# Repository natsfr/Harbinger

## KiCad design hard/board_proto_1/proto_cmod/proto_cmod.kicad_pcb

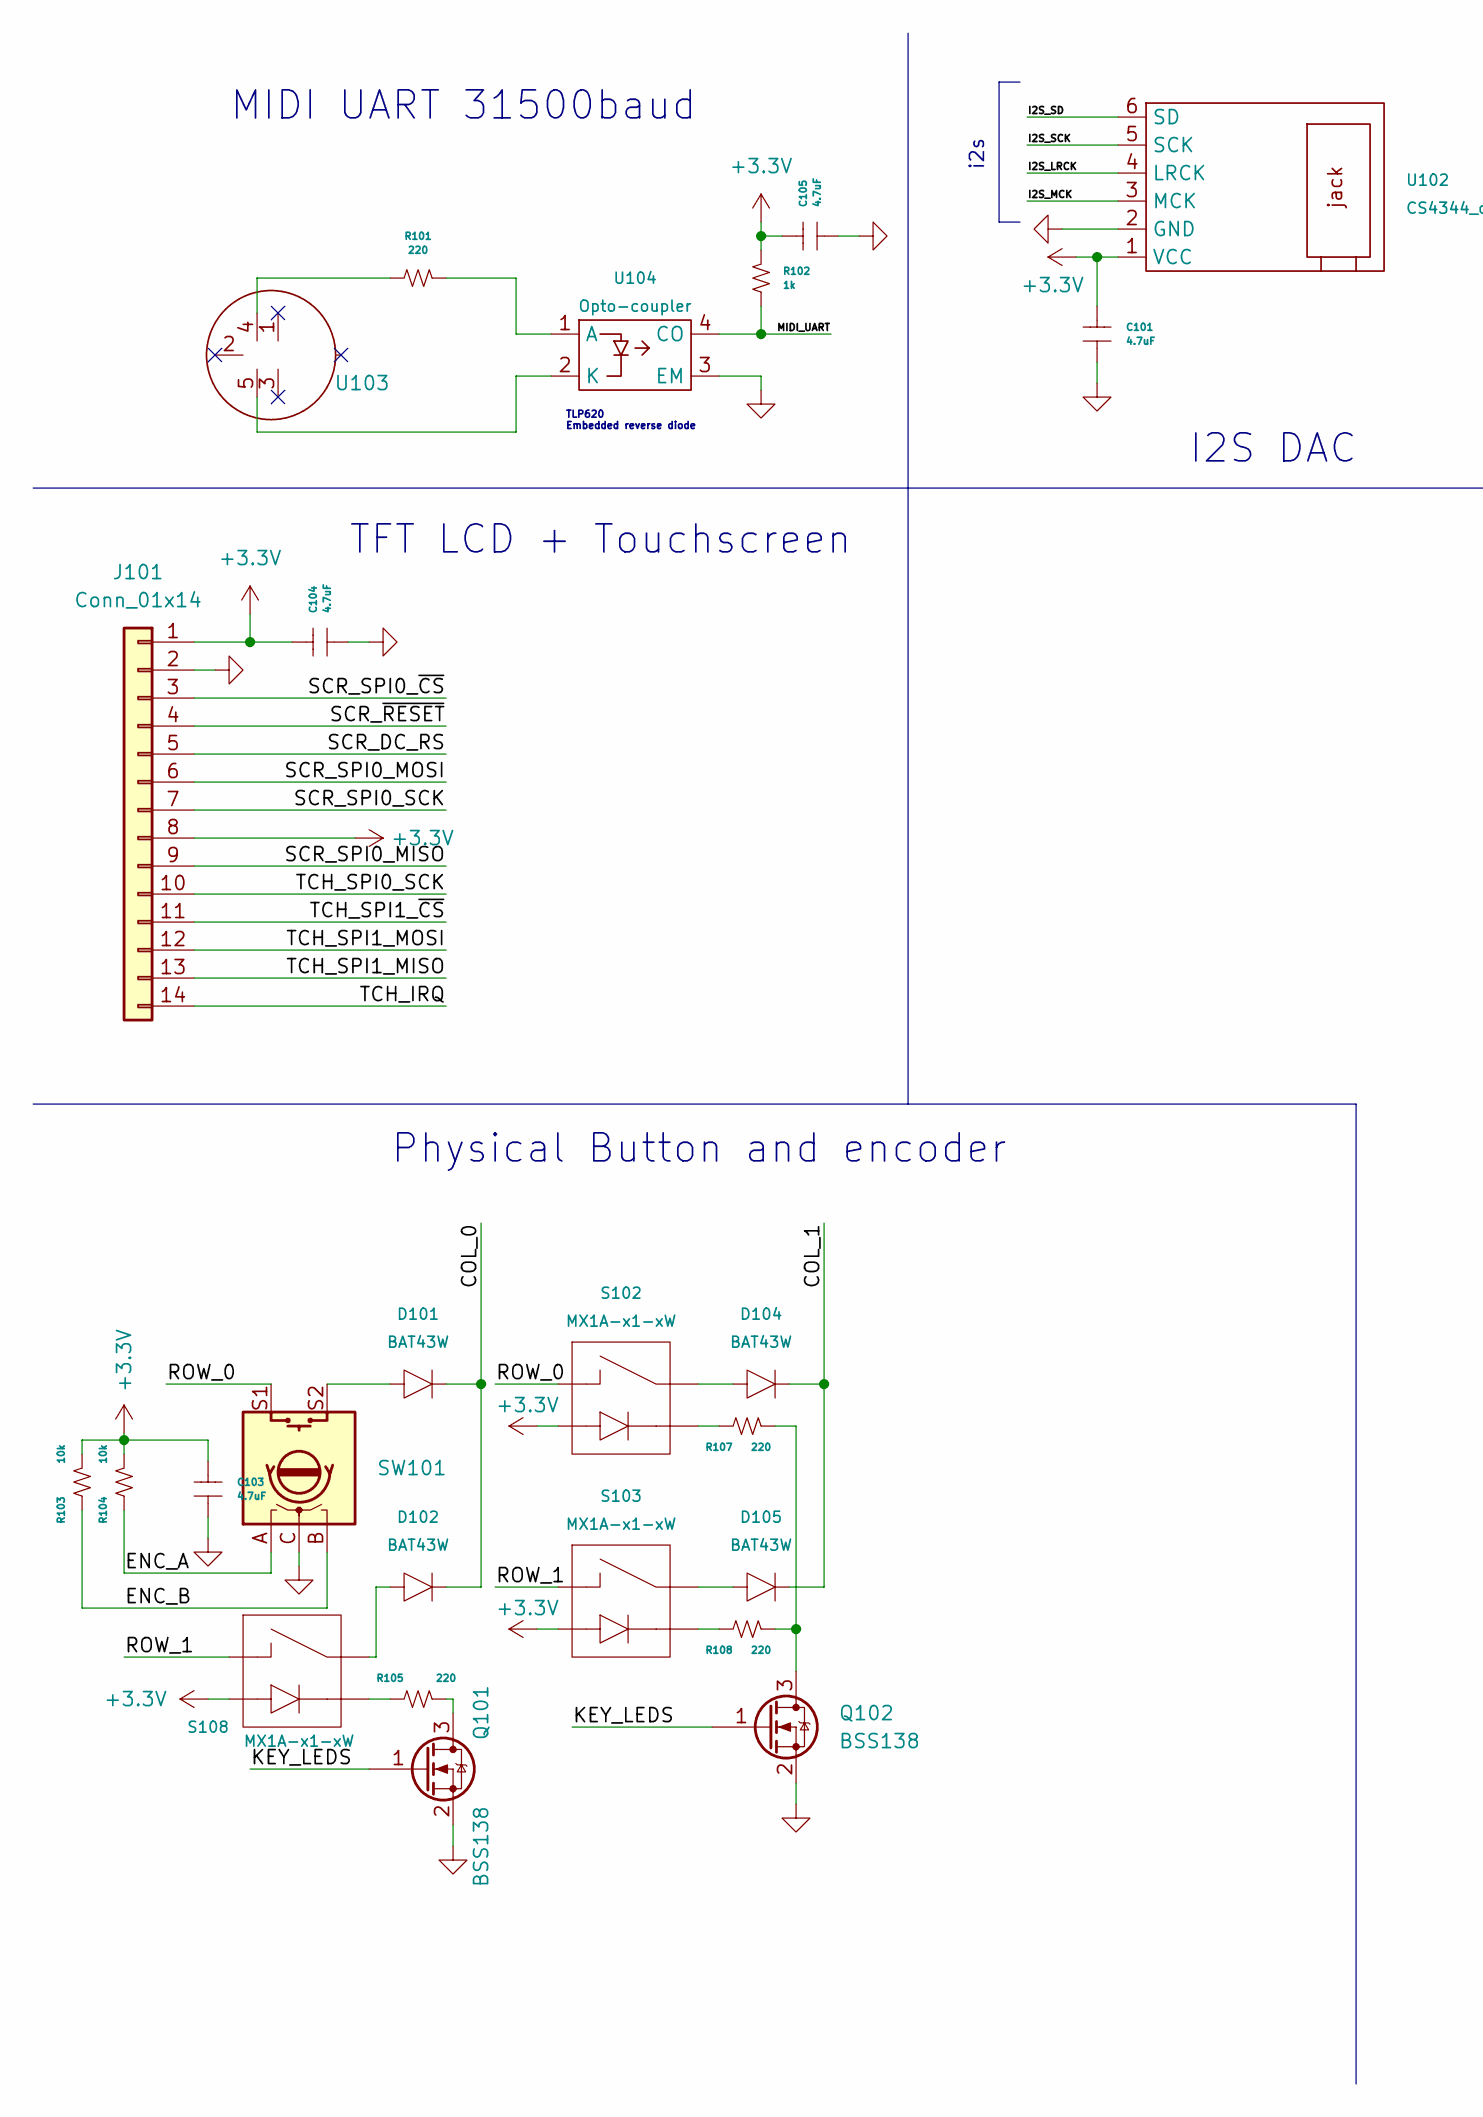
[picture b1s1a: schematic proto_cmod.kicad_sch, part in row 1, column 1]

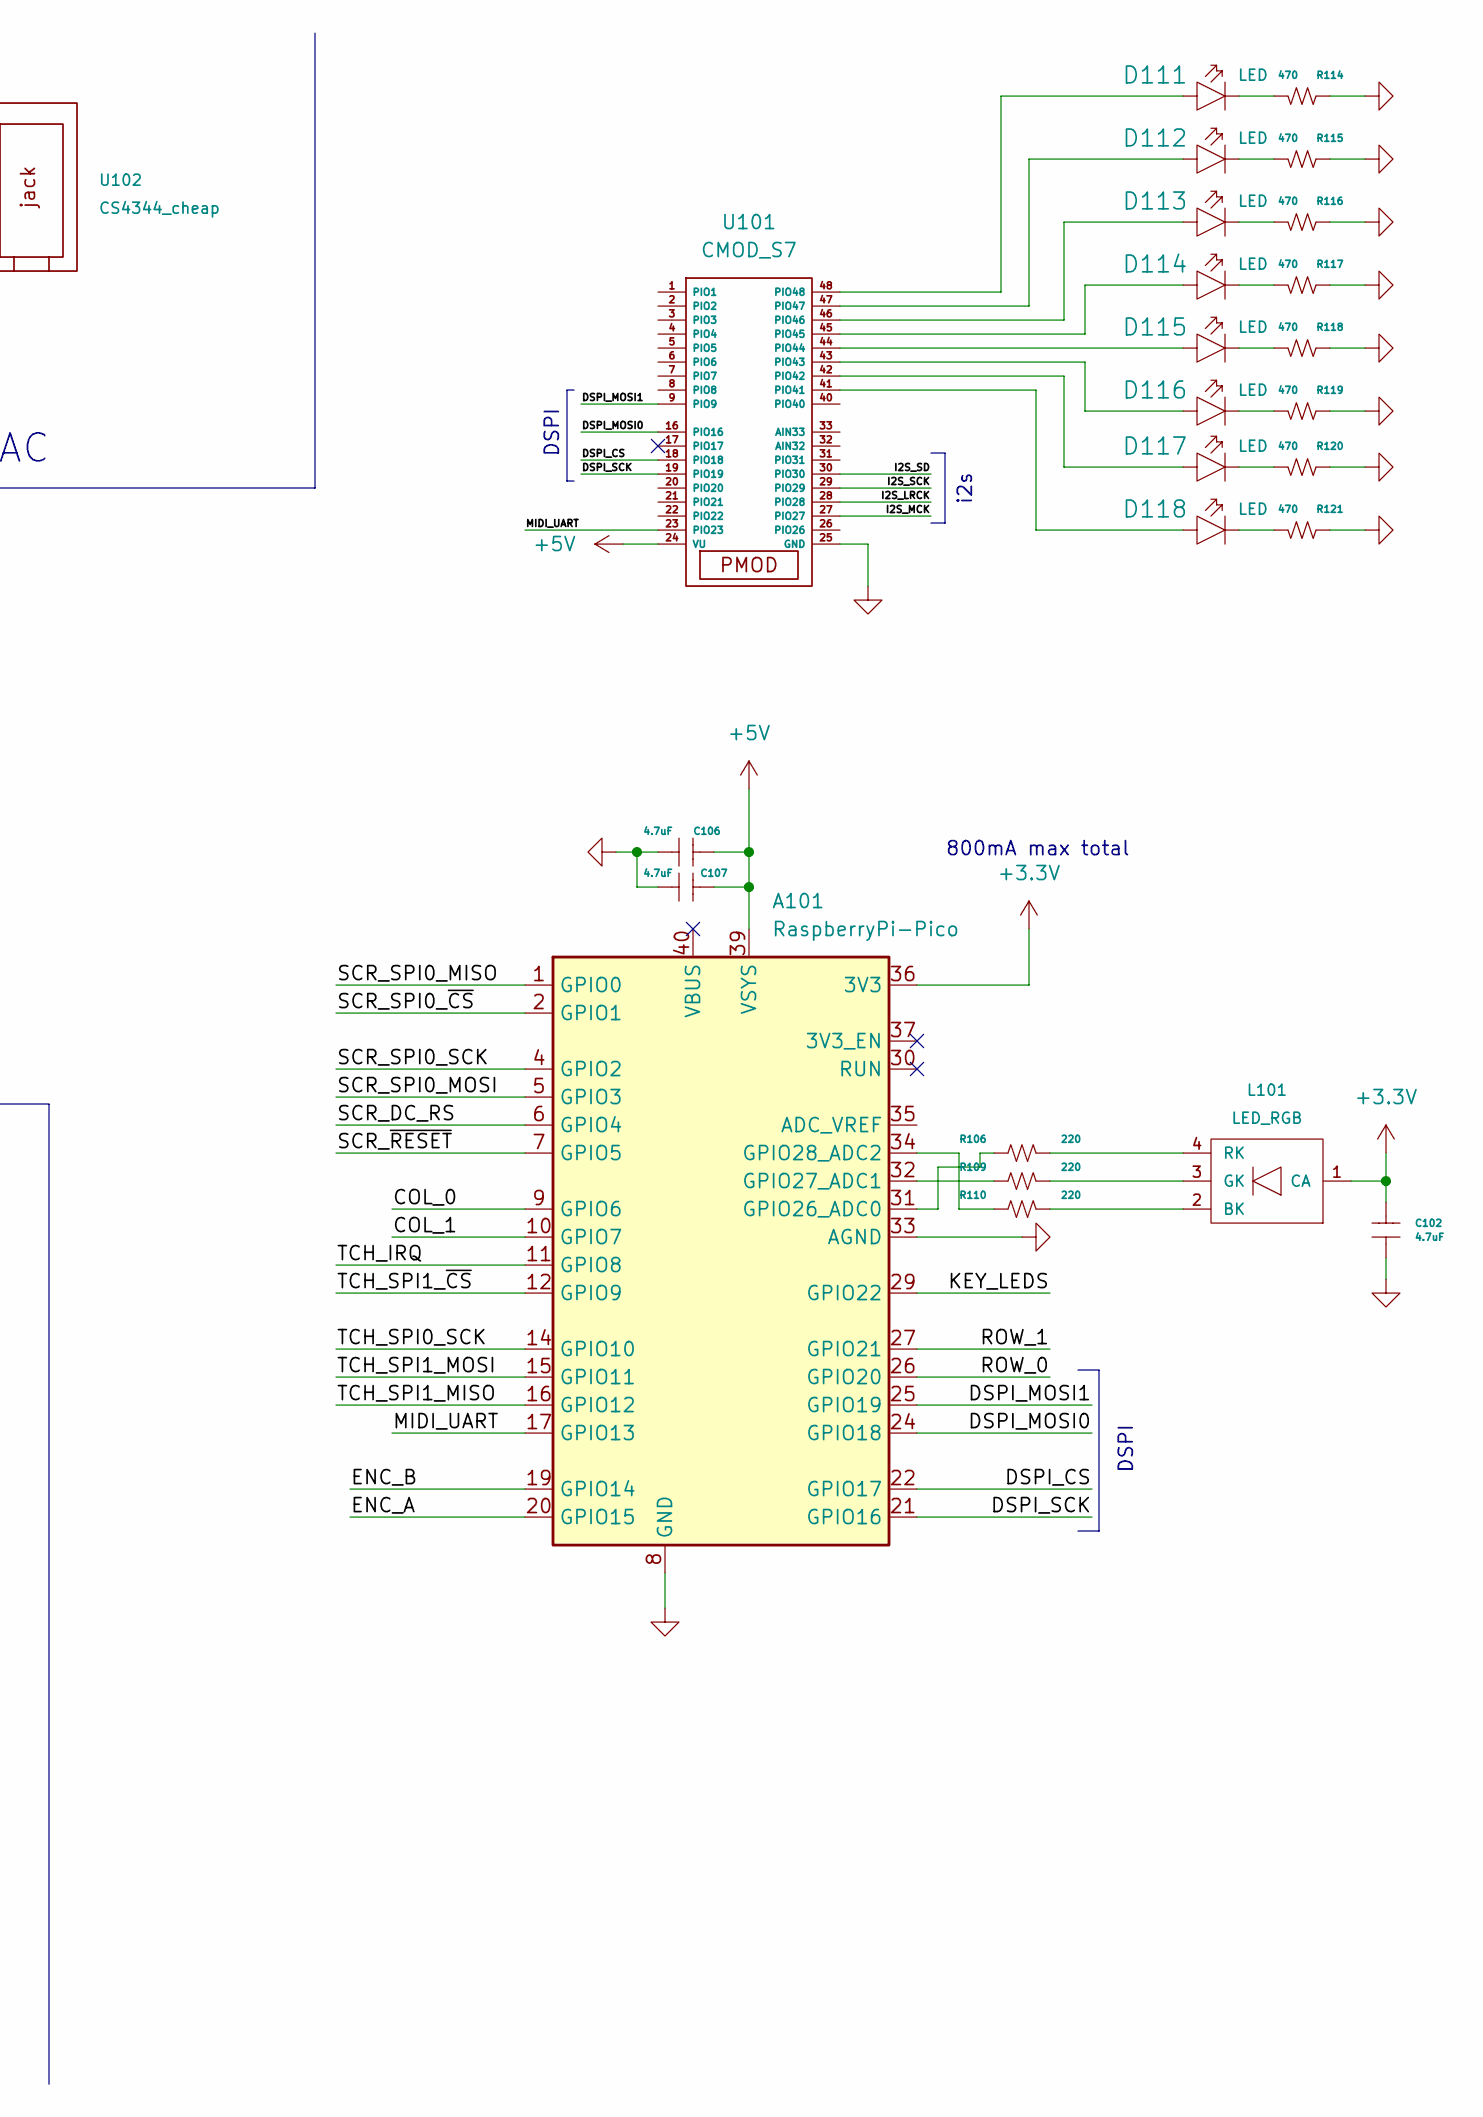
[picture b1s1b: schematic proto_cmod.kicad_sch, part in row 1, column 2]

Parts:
A101: RaspberryPi-Pico; Raspberry_Pi_Pico_THT
C101, C102, C103, C104, C105, C106, C107: 4.7uF; SM0805
D101, D102, D104, D105: BAT43W; SOD-123
D111, D112, D113, D114, D115, D116, D117, D118: LED; LED-0603
J101: Conn_01x14; ILI9341_MSP2807
L101: LED_RGB; CLMVC-FKA_RGBLED
Q101, Q102: BSS138; SOT-23
R101, R105, R106, R107, R108, R109, R110: 220; SM0603
R102: 1k; SM0603
R103, R104: 10k; SM0603
R114, R115, R116, R117, R118, R119, R120, R121: 470; SM0603
S102, S103, S108: MX1A-x1-xW
SW101: RotaryEncoder_Switch; RotaryEncoder_Alps_EC12E-Switch_Vertical_H20mm_CircularMoun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
U101: CMOD_S7; MOD_CMOD_S7
U102: CS4344_cheap; pin_array_6x1
U103: Lumberg_0105_05; Lumberg_010505
U104: Opto-coupler; TLP620

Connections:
+3V3: A101.36 (3V3), C101.2, C102.2, C103.2, C104.2, C105.2, J101.1, J101.8, L101.1 (CA), R102.2, R103.2, R104.2, S102.3, S103.3, S108.3, U102.1 (VCC)
+5V: A101.39 (VSYS), C106.2, C107.2, U101.24 (VU)
/COL_0: A101.9 (GPIO6), D101.K, D102.K
/COL_1: A101.10 (GPIO7), D104.K, D105.K
/DSPI_CS: A101.22 (GPIO17), U101.18 (PIO18)
/DSPI_MOSI0: A101.24 (GPIO18), U101.16 (PIO16)
/DSPI_MOSI1: A101.25 (GPIO19), U101.9 (PIO9)
/DSPI_SCK: A101.21 (GPIO16), U101.19 (PIO19)
/ENC_A: A101.20 (GPIO15), R104.1, SW101.A
/ENC_B: A101.19 (GPIO14), R103.1, SW101.B
/I2S_LRCK: U101.28 (PIO28), U102.4 (LRCK)
/I2S_MCK: U101.27 (PIO27), U102.3 (MCK)
/I2S_SCK: U101.29 (PIO29), U102.5 (SCK)
/I2S_SD: U101.30 (PIO30), U102.6 (SD)
/KEY_LEDS: A101.29 (GPIO22), Q101.1 (G), Q102.1 (G)
/MIDI_UART: A101.17 (GPIO13), R102.1, U101.23 (PIO23), U104.4 (CO)
/ROW_0: A101.26 (GPIO20), S102.1, SW101.S1
/ROW_1: A101.27 (GPIO21), S103.1, S108.1
/SCR_DC_RS: A101.6 (GPIO4), J101.5
/SCR_SPI0_MISO: A101.1 (GPIO0), J101.9
/SCR_SPI0_MOSI: A101.5 (GPIO3), J101.6
/SCR_SPI0_SCK: A101.4 (GPIO2), J101.7
/SCR_SPI0_~CS: A101.2 (GPIO1), J101.3
/SCR_~RESET: A101.7 (GPIO5), J101.4
/TCH_IRQ: A101.11 (GPIO8), J101.14
/TCH_SPI0_SCK: A101.14 (GPIO10), J101.10
/TCH_SPI1_MISO: A101.16 (GPIO12), J101.13
/TCH_SPI1_MOSI: A101.15 (GPIO11), J101.12
/TCH_SPI1_~CS: A101.12 (GPIO9), J101.11
GND: A101.3 (GND), A101.8 (GND), A101.13 (GND), A101.18 (GND), A101.23 (GND), A101.28 (GND), A101.33 (AGND), A101.38 (GND), C101.1, C102.1, C103.1, C104.1, C105.1, C106.1, C107.1, J101.2, Q101.2 (S), Q102.2 (S), R114.1, R115.1, R116.1, R117.1, R118.1, R119.1, R120.1, R121.1, SW101.C, U101.25 (GND), U102.2 (GND), U104.3 (EM)
unnamed: A101.31 (GPIO26_ADC0), R106.1
unnamed: D101.A, SW101.S2
unnamed: D102.A, S108.2
unnamed: D104.A, S102.2
unnamed: D105.A, S103.2
unnamed: D111.A, U101.48 (PIO48)
unnamed: D111.K, R114.2
unnamed: D112.A, U101.47 (PIO47)
unnamed: D112.K, R115.2
unnamed: D113.A, U101.46 (PIO46)
unnamed: D113.K, R116.2
unnamed: D114.A, U101.45 (PIO45)
unnamed: D114.K, R117.2
unnamed: D115.A, U101.44 (PIO44)
unnamed: D115.K, R118.2
unnamed: D116.A, U101.43 (PIO43)
unnamed: D116.K, R119.2
unnamed: D117.A, U101.42 (PIO42)
unnamed: D117.K, R120.2
unnamed: D118.A, U101.41 (PIO41)
unnamed: D118.K, R121.2
unnamed: L101.2 (BK), R110.2
unnamed: L101.3 (GK), R109.2
unnamed: L101.4 (RK), R106.2
unnamed: Q101.3 (D), R105.2
unnamed: Q102.3 (D), R107.2, R108.2
unnamed: R101.1, U103.4
unnamed: R101.2, U104.1 (A)
unnamed: R105.1, S108.4
unnamed: R107.1, S102.4
unnamed: R108.1, S103.4
unnamed: A101.32 (GPIO27_ADC1), R109.1
unnamed: A101.34 (GPIO28_ADC2), R110.1
unnamed: U103.5, U104.2 (K)

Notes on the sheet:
MIDI UART 31500baud
DSPI
800mA max total
i2s
TLP620 Embedded reverse diode
I2S DAC
TFT LCD + Touchscreen
Physical Button and encoder

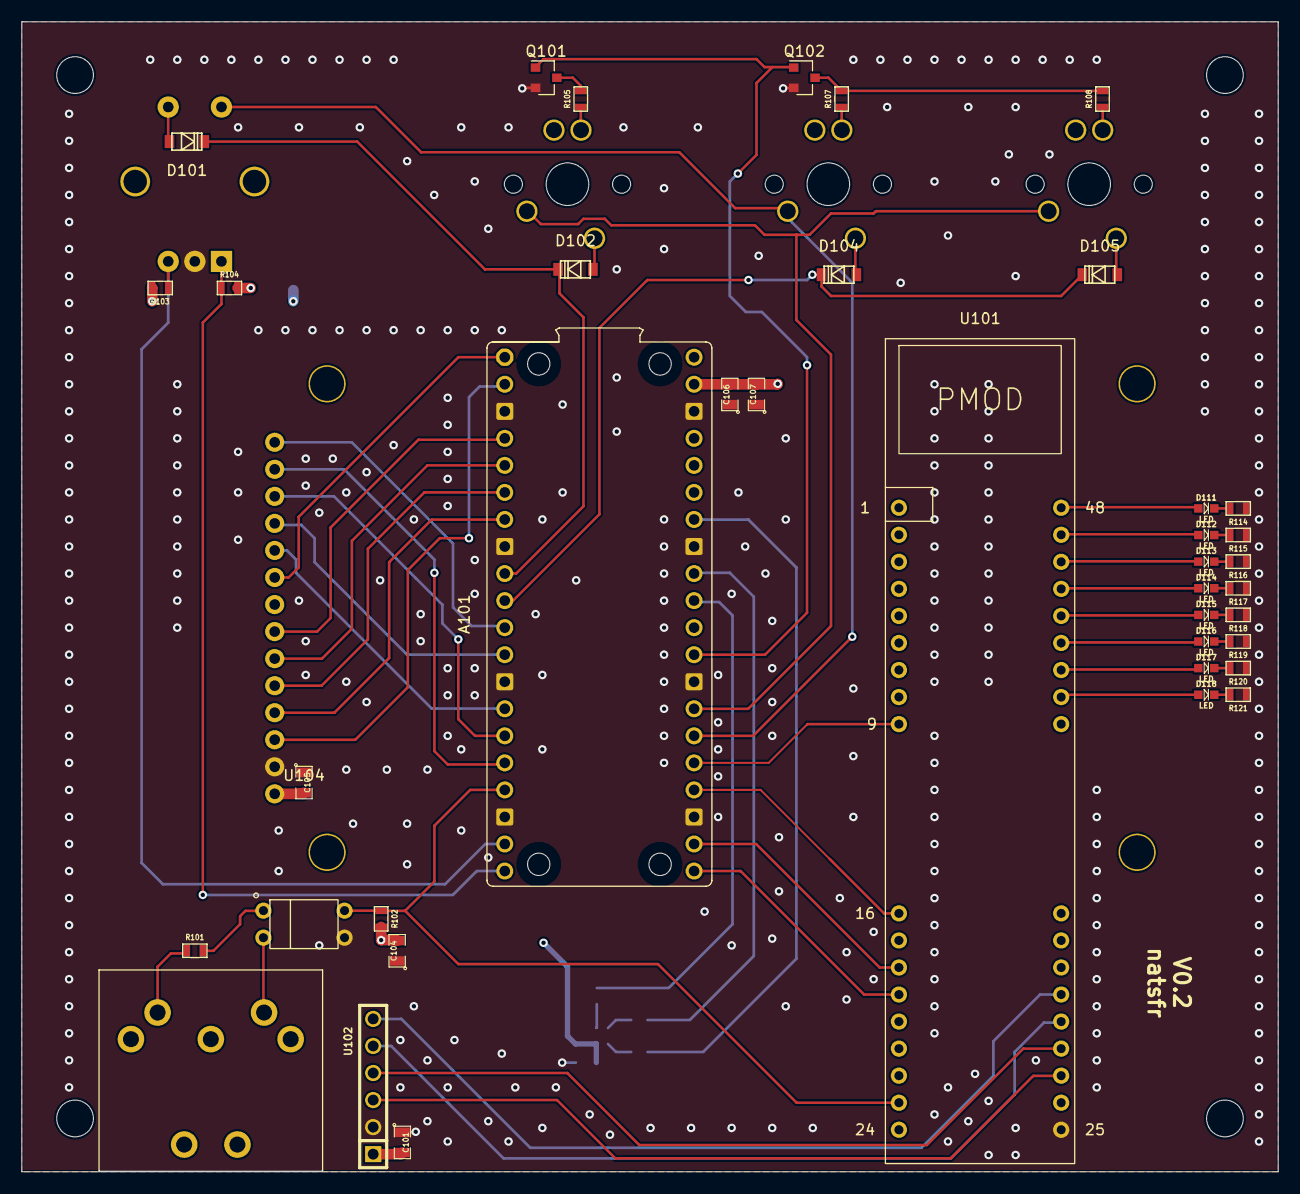
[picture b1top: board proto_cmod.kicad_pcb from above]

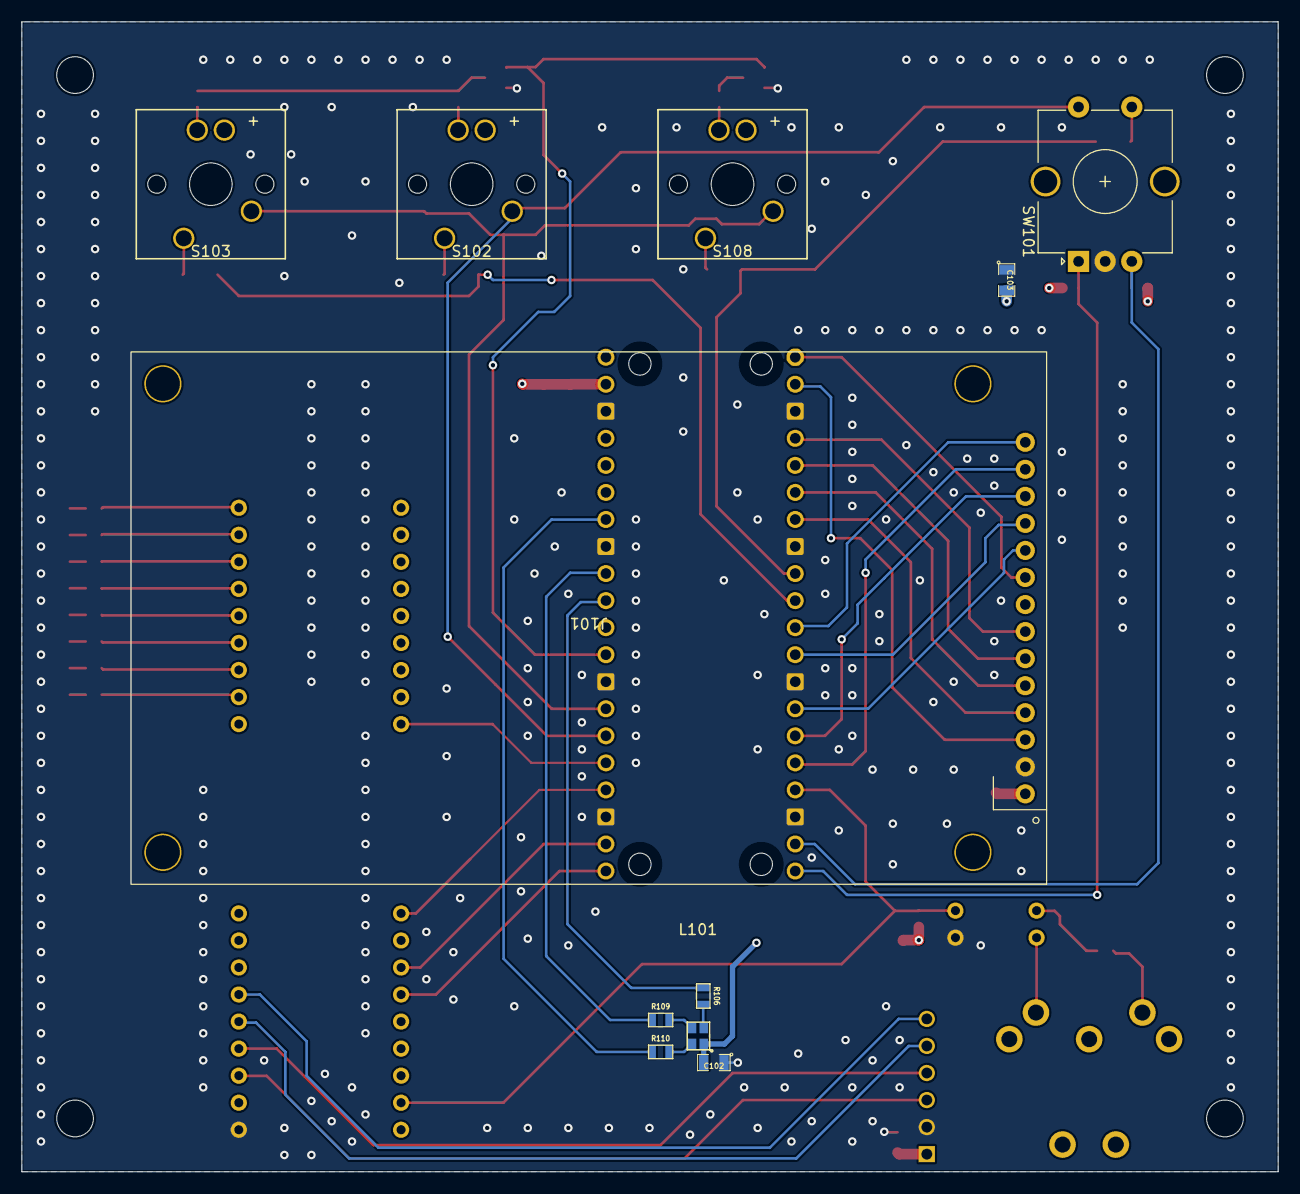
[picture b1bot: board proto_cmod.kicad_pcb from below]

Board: 4 copper layers, 118.0 x 108.0 mm, 50 parts (11 on the bottom side), 64 nets.

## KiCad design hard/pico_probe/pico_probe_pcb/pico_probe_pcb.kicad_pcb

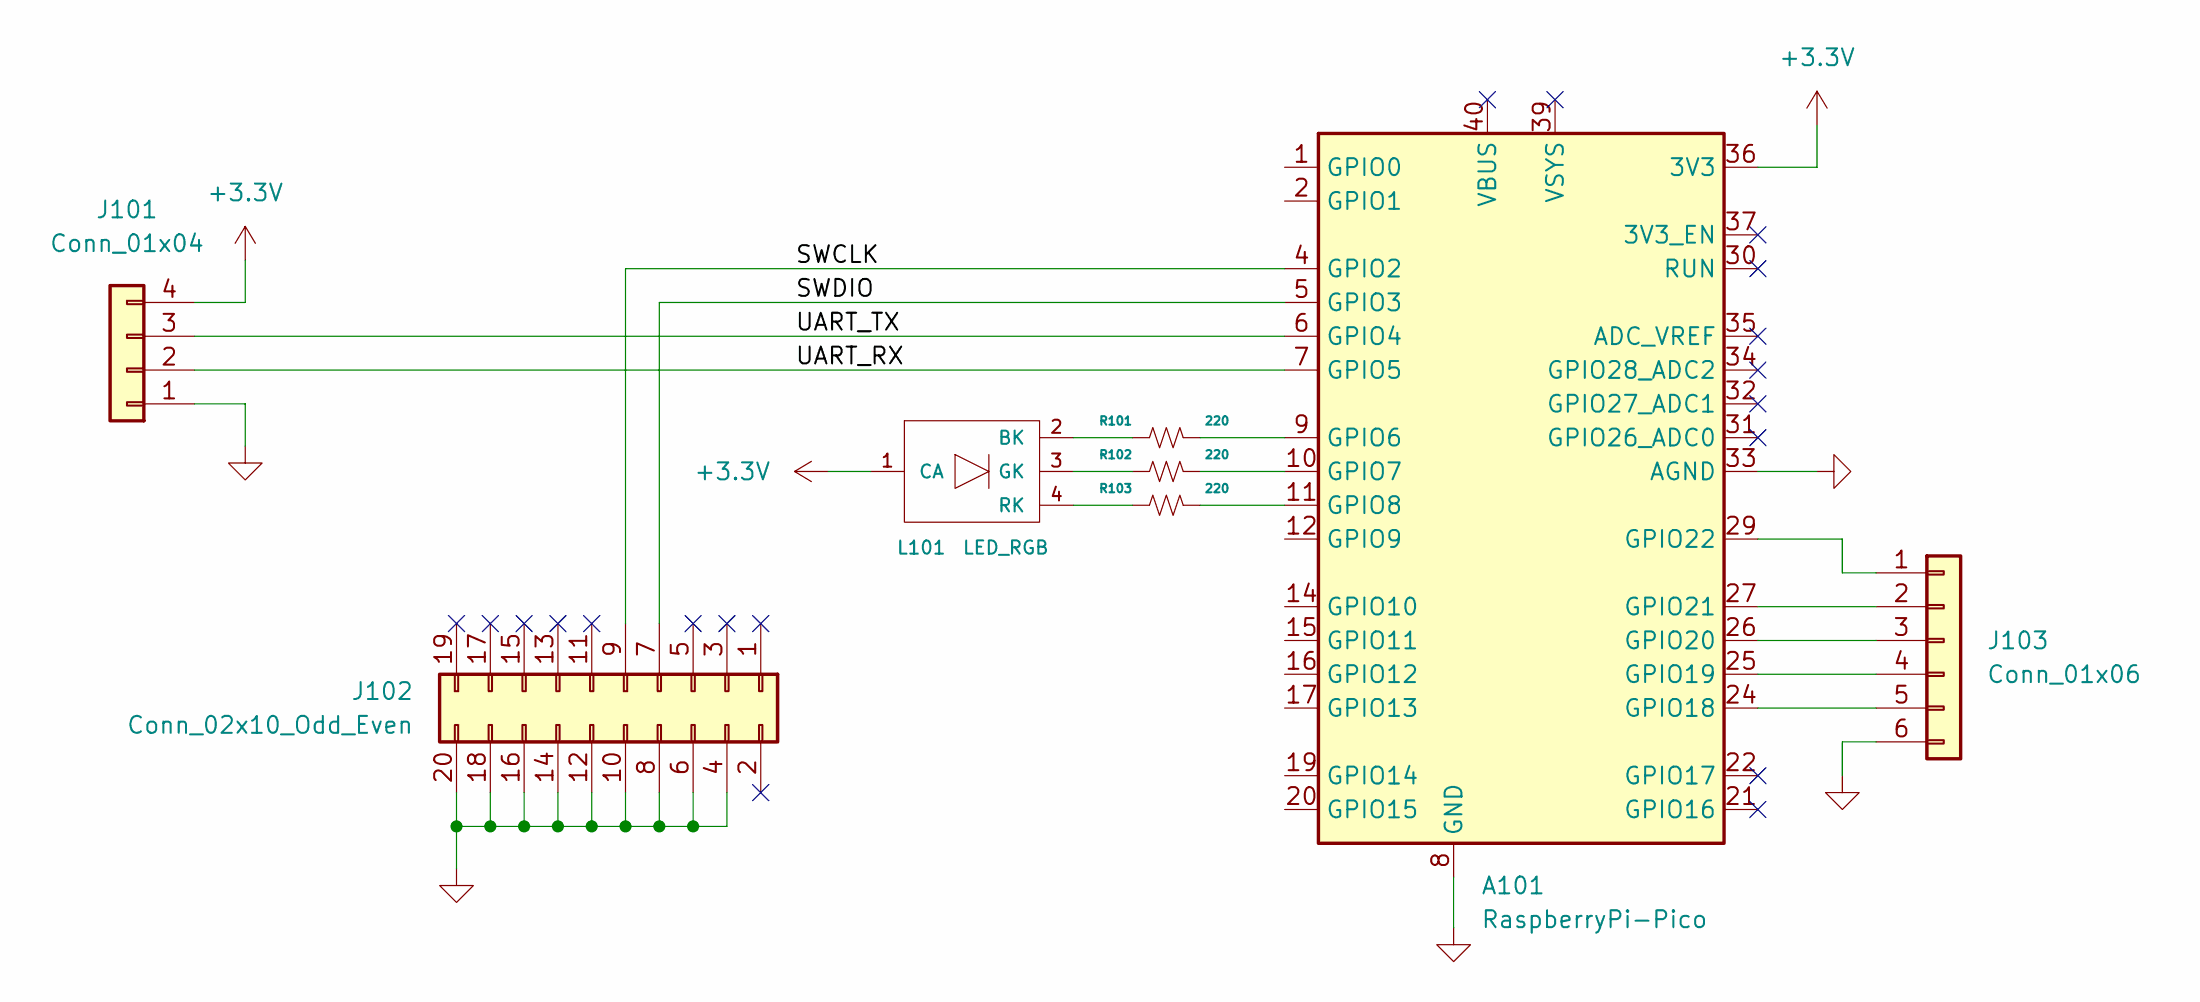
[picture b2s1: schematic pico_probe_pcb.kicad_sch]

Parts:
A101: RaspberryPi-Pico; Raspberry_Pi_Pico_AddOn
J101: Conn_01x04; JST_XH_B4B-XH-A_1x04_P2.50mm_Vertical
J102: Conn_02x10_Odd_Even; PinSocket_2x10_P2.54mm_Vertical
J103: Conn_01x06; PinSocket_1x06_P2.54mm_Vertical
L101: LED_RGB; CLMVC-FKA_RGBLED
R101, R102, R103: 220; SM0402

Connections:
+3V3: A101.36 (3V3), J101.4, L101.1 (CA)
/SWCLK: A101.4 (GPIO2), J102.9
/SWDIO: A101.5 (GPIO3), J102.7
/UART_RX: A101.7 (GPIO5), J101.2
/UART_TX: A101.6 (GPIO4), J101.3
GND: A101.3 (GND), A101.8 (GND), A101.13 (GND), A101.18 (GND), A101.23 (GND), A101.28 (GND), A101.33 (AGND), A101.38 (GND), J101.1, J102.4, J102.6, J102.8, J102.10, J102.12, J102.14, J102.16, J102.18, J102.20, J103.6
unnamed: A101.9 (GPIO6), R101.2
unnamed: A101.10 (GPIO7), R102.2
unnamed: A101.11 (GPIO8), R103.2
unnamed: A101.24 (GPIO18), J103.5
unnamed: A101.25 (GPIO19), J103.4
unnamed: A101.26 (GPIO20), J103.3
unnamed: A101.27 (GPIO21), J103.2
unnamed: A101.29 (GPIO22), J103.1
unnamed: L101.2 (BK), R101.1
unnamed: L101.3 (GK), R102.1
unnamed: L101.4 (RK), R103.1

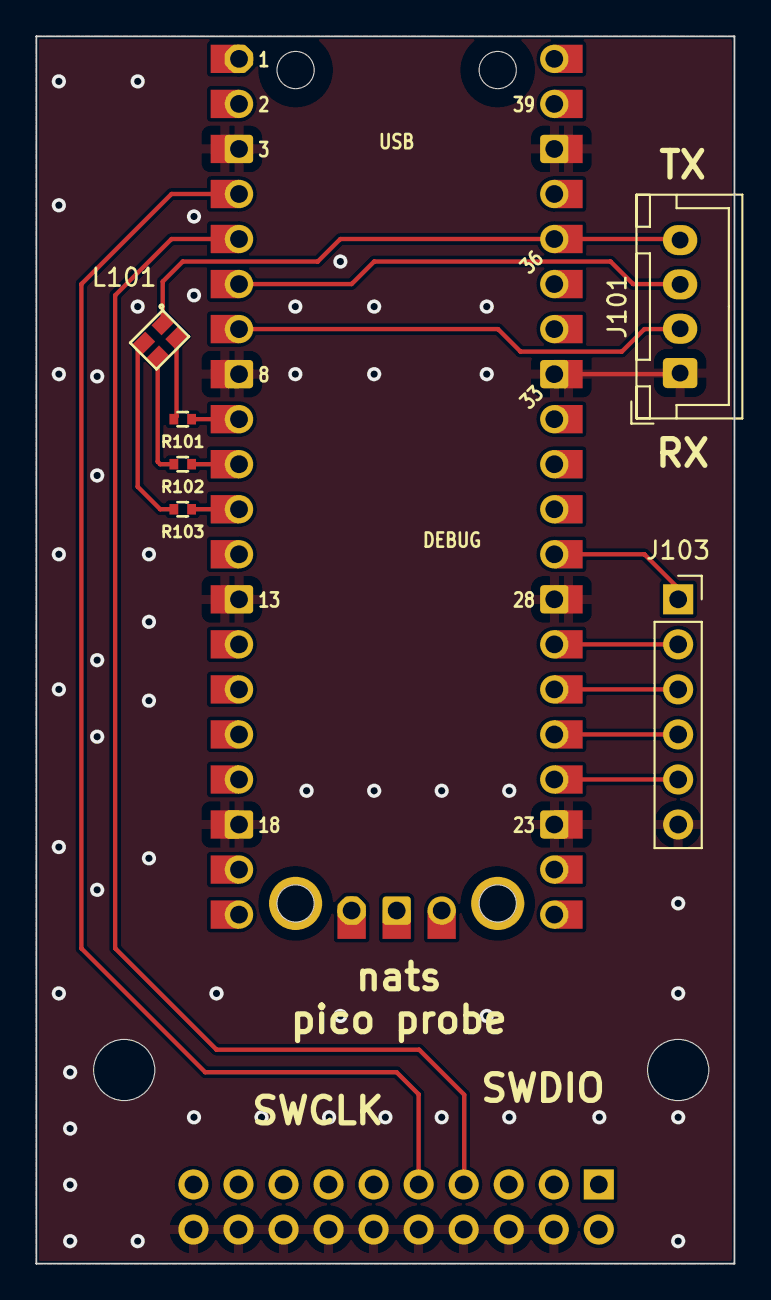
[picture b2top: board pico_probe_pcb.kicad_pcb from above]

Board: 2 copper layers, 39.4 x 69.2 mm, 8 parts (1 on the bottom side), 17 nets.

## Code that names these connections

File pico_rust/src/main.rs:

//! # Pico Blinky Example
//!
//! Blinks the LED on a Pico board.
//!
//! This will blink an LED attached to GP25, which is the pin the Pico uses for
//! the on-board LED.
//!
//! See the `Cargo.toml` file for Copyright and license details.

#![no_std]
#![no_main]

#[macro_use(block)]
extern crate nb;

mod ili9341screen;
mod fpga;
mod frame_buffer;
mod keys;
mod rgb_led;
mod midi;
mod voices;

use core::cell::RefCell;
use fpga::FpgaLink;
use fugit::RateExtU32;
use cortex_m::interrupt::Mutex;
use frame_buffer::Drawer;
use fugit::MicrosDurationU32;
use hal::Spi;
use hal::gpio::{FunctionPio0, Pin};
use hal::pwm::FreeRunning;
use hal::pwm::Slices;
use hal::timer::Alarm;
use hal::timer::Alarm0;
use ili9341screen::Screen;
use keys::Keys;
use midi::MidiUart;
use rgb_led::RgbLed;
// The macro for our start-up function
//use rp_pico::entry;
use hal::pac::interrupt;

// Ensure we halt the program on panic (if we don't mention this crate it won't
// be linked)
use panic_halt as _;

// Pull in any important traits
use rp_pico::hal::prelude::*;

// A shorter alias for the Peripheral Access Crate, which provides low-level
// register access
use rp_pico::hal::pac;

// A shorter alias for the Hardware Abstraction Layer, which provides
// higher-level drivers.
use rp_pico::hal;
use voices::VoiceManager;

// Using PIO for custom fast spi
use hal::pio::{PIOExt, ShiftDirection};
use hal::dma::{double_buffer, single_buffer, DMAExt};

const KEY_POL_RATE: MicrosDurationU32 =
    MicrosDurationU32::millis(10);

/// Store the key abstraction to be regularly queried
static G_KEYS: Mutex<RefCell<Option<Keys>>> = Mutex::new(RefCell::new(None));
static mut G_ALARM0 : Option<Alarm0> = None;

#[interrupt]
fn TIMER_IRQ_0() {
    cortex_m::interrupt::free(|cs| {
        let ref mut g_keys = G_KEYS.borrow(cs).borrow_mut();

        if let Some(keys) = g_keys.as_mut() {
            keys.read_all()
        }

        unsafe {
            if let Some(alarm0) = G_ALARM0.as_mut() {
                alarm0.clear_interrupt();
            }
        }
    });
}

fn read_last_key() -> Option<u8>{
    let mut out = None;

    cortex_m::interrupt::free(|cs| {
        let ref mut g_keys = G_KEYS.borrow(cs).borrow();

        if let Some(keys) = g_keys.as_ref() {
            out = Some(keys.actual())
        }
    });

    out
}

fn setup_pwm<PWM : hal::pwm::SliceId>(mut pwm : hal::pwm::Slice<PWM, FreeRunning>)
    -> hal::pwm::Slice<PWM, FreeRunning>{
    pwm.set_ph_correct();
    pwm.enable();
    pwm
}

/// basic screen drawing to at least display somthing, move elsewhere, do something
/// else with it completly
fn stupid_screen_draw() {
    let mut x : usize = 0;
    let mut prev_key : usize = 0;

    Drawer::clear();

    Drawer::rect(x, 0, 30, 2, 0xFFF0);
    x = (x + 4) % (ili9341screen::WIDTH + 30);

    let key = read_last_key().unwrap();
    if key != 0 {
        Drawer::rect(key as usize * 20, 120, 4, 4, 0xFFFF);
        prev_key = key as usize;
    }

    if prev_key != 0 {
        Drawer::rect(prev_key * 20, 80, 4, 4, 0xFF00);
    }
}

/// Entry point to our bare-metal application.
///
/// The `#[entry]` macro ensures the Cortex-M start-up code calls this function
/// as soon as all global variables are initialised.
///
/// The function configures the RP2040 peripherals, then blinks the LED in an
/// infinite loop.
#[rp2040_hal::entry]
fn main() -> ! {
    unsafe { cortex_m::interrupt::enable(); }

    // Grab our singleton objects
    let mut pac = pac::Peripherals::take().unwrap();
    // let core = pac::CorePeripherals::take().unwrap();

    // Set up the watchdog driver - needed by the clock setup code
    let mut watchdog = hal::Watchdog::new(pac.WATCHDOG);

    // Configure the clocks
    //
    // The default is to generate a 125 MHz system clock
    let clocks = hal::clocks::init_clocks_and_plls(
        rp_pico::XOSC_CRYSTAL_FREQ,
        pac.XOSC,
        pac.CLOCKS,
        pac.PLL_SYS,
        pac.PLL_USB,
        &mut pac.RESETS,
        &mut watchdog,
    )
    .ok()
    .unwrap();

    // The delay object lets us wait for specified amounts of time (in
    // milliseconds)
    // let mut delay = cortex_m::delay::Delay::new(core.SYST, clocks.system_clock.freq().to_Hz());

    // The single-cycle I/O block controls our GPIO pins
    let sio = hal::Sio::new(pac.SIO);

    // Set the pins up according to their function on this particular board
    /* what that shit example are not giving the same ! */
    /*let pins = rp_pico::Pins::new(
        pac.IO_BANK0,
        pac.PADS_BANK0,
        sio.gpio_bank0,
        &mut pac.RESETS,
    );*/
    let pins = hal::gpio::Pins::new(
        pac.IO_BANK0,
        pac.PADS_BANK0,
        sio.gpio_bank0,
        &mut pac.RESETS,
    );

    let rate  = clocks.peripheral_clock.freq();

    let spi =
        Spi::<_, _, 8>::new(pac.SPI0)
            .init(
                &mut pac.RESETS,
                rate, 
                (20_000 * 1000).Hz(),
                &embedded_hal::spi::MODE_0);


    // Init PWMs
    let pwm_slices = Slices::new(pac.PWM, &mut pac.RESETS);

    let mut timer = rp2040_hal::Timer::new(pac.TIMER, &mut pac.RESETS);
    let mut screen = Screen::init_partial(
        pins.gpio0,
        pins.gpio1,
        pins.gpio2,
        pins.gpio3,
        pins.gpio4,
        pins.gpio5,
        spi,
        &mut timer);

    let mut rgbled = RgbLed::init(
        setup_pwm(pwm_slices.pwm6),
        setup_pwm(pwm_slices.pwm5),
        pins.gpio26,
        pins.gpio27,
        pins.gpio28);

    rgbled.low();

    let mut midi_uart =
        MidiUart::init(
            pac.UART0,
            pins.gpio13,
            rate,
            &mut pac.RESETS,
            Some(rgbled));


    let keys = Keys::init_partial(
        pins.gpio6,
        pins.gpio7,
        pins.gpio20,
        pins.gpio21,
        None
    );

    cortex_m::interrupt::free(|cs| {
        G_KEYS.borrow(cs).replace(Some(keys))
    });

    // Unmask the timer0 IRQ so that it will generate an interrupt
    let mut alarm0 = timer.alarm_0().unwrap();
    alarm0.schedule(KEY_POL_RATE).unwrap();
    alarm0.enable_interrupt();

    // we create a voice manager on midi channel 0
    let mut voice_manager =
        VoiceManager::default_on_midi_channel(0);

    let (pio, sm0, _, _, _) =
        pac.PIO0.split(&mut pac.RESETS);

    let mut fpga_link = FpgaLink::new(
        pio,
        sm0,
        pac.DMA.split(&mut pac.RESETS),
        pins.gpio16,
        pins.gpio17,
        pins.gpio18,
        pins.gpio19);

    // We use single buffer for this one triggered by note send and configuration of voice


    unsafe {
        pac::NVIC::unmask(pac::Interrupt::TIMER_IRQ_0);
        G_ALARM0 = Some(alarm0);
    }

    // we draw at least once
    stupid_screen_draw();

    loop {
        midi_uart.feed_data_into_parser();

        while let Some(midi_command) = midi_uart.try_read_command() {
            voice_manager.handle_midi_command(&mut fpga_link, midi_command)
        }

        // screen.push_frame();
        cortex_m::interrupt::free(|cs| {
            unsafe {
                if let Some(alarm0) = G_ALARM0.as_mut() {
                    if alarm0.finished() {
                        alarm0.schedule(KEY_POL_RATE).unwrap();
                    }
                }
            }
        });
    }
}

// End of file

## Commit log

2022-12-17 First commit, working on the FM Engine
2022-12-22 starting midi parser
2022-12-26 First prototype of 2 voice 2 operator FM. Switching to spartan7
2022-12-29 Working version ported to spartan7
2023-01-02 Starting to port the midi control to the pi pico - shitty commit full of crap
2023-01-07 31.5MHz dual spi lane using PIO seems to work
2023-01-22 backup before cleaning branch
2023-01-26 basic crappy template system to test patch gen output
2023-02-26 last crap commit
2023-03-31 huge pile of shit
2023-04-02 Adding code related to screen handling, probably misconfigured
2023-04-02 Trying to map ili9341 configuration to the mapping in proto_cmod.pdf
2023-04-05 Something to display and problematic key query
2023-04-05 Not crashing but now other rect either
2023-04-05 Querying both rows
2023-04-10 Rust skeleton
2023-04-10 Adding missing link file
2023-04-10 Flashing through rust tooling works OK, need to start port now
2023-04-10 Screen SPI handling (wip)
2023-04-22 Ongoing replication of base system
2023-04-24 Semi working screen
2023-04-25 static, not const, raaaaah
2023-04-26 configuration for live probe debugging in vscode
2023-04-26 Using a working frequency for spi
2023-05-01 Making rust compile with preparatory work for correct key polling
2023-05-06 Adding sun-like LED
    PWM doesn't look like it's correctly configured
2023-05-07 Correct PWM control of the led
2023-05-07 Pushing last timer usage
2023-05-07 Correct alarm behaviour for key polling
2023-05-13 Premature and completly incomplete implementation of MIDI parsing
    Damnit corentin
2023-05-16 Global parsing & validation ready for midi (todo: voice assignment)
2023-05-19 saving HDL v2 bad state
2023-05-21 Crapouillo FPGA V2 and soft. So sorry for the commit.
2023-05-22 Updating rust FPGA definitions
2023-05-23 Adding Midi UART initialization rust side
2023-05-23 Setting in place midi polling/parsing
2023-05-25 Half tested Velocity/Amp modulation and Oneshot/cyclic ADSR
2023-05-27 Starting rust from scratch
2023-05-27 Starting a basic voice manager
2023-05-27 Up to the pain point of correctly setting the DMA for the FPGA
2023-06-01 PIO written, needs DMA
2023-06-16 Bumping deps
2023-06-16 Moving stuff around (not connected)
2023-08-21 Reading midi bytes at the correct rate
2023-08-21 Fixing stupidities in midi parser, works okish
2024-10-21 Test
